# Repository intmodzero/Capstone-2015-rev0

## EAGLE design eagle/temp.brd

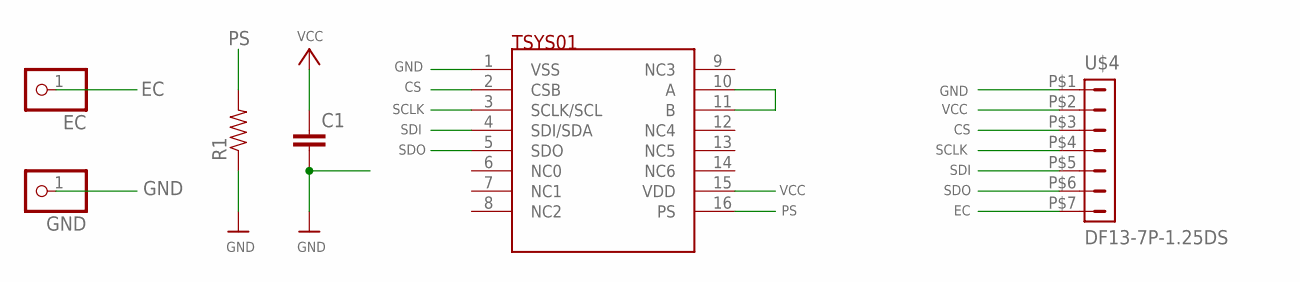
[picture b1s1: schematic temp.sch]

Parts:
C1: CAP0402-CAP; 0402-CAP
EC: PINHD-1X1; 1X01
GND: PINHD-1X1; 1X01
R1: RESISTOR0402-RES; 0402-RES
U$1: TSYS01; QFN16
U$4: DF13-7P-1.25DS

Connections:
CS: U$1.2 (CSB), U$4.P$3 (3)
EC: EC.1, U$4.P$7 (7)
GND: C1.2, GND.1, R1.1, U$1.1 (VSS), U$4.P$1 (1)
unnamed: U$1.10 (A), U$1.11 (B)
PS: R1.2, U$1.16 (PS)
SCLK: U$1.3 (SCLK/SCL), U$4.P$4 (4)
SDI: U$1.4 (SDI/SDA), U$4.P$5 (5)
SDO: U$1.5 (SDO), U$4.P$6 (6)
VCC: C1.1, U$1.15 (VDD), U$4.P$2 (2)

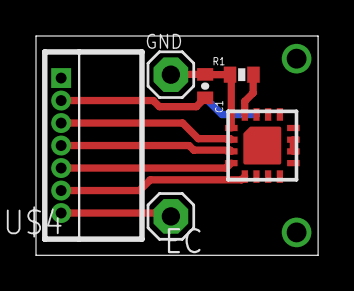
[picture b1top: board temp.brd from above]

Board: 2 copper layers, 15.7 x 12.2 mm, 6 parts (0 on the bottom side), 9 nets.

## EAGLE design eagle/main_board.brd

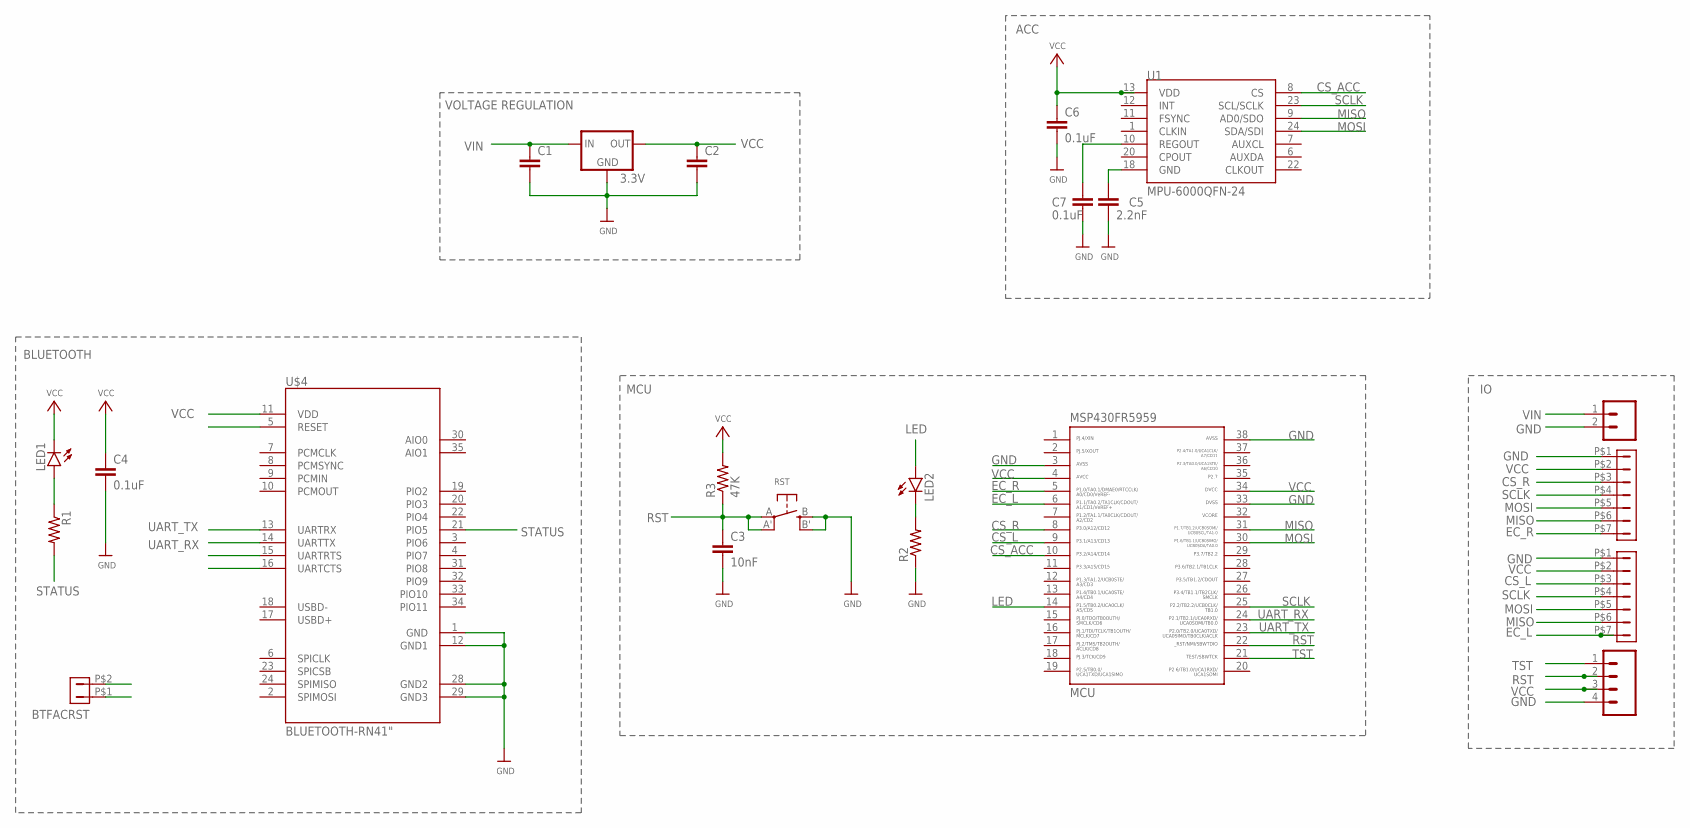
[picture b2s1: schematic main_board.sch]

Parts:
3.3V: V_REG_78XX; SOT223
5V: M02-JST-2-PTH-NO_SILK; JST-2-PTH-NS
BTFACRST: DF13-2P-1.25DSA
C1, C2: CAP0603-CAP; 0603-CAP
C3: 10nF; 0603-CAP
C4: 0.1uF; 0603-CAP
C5: 2.2nF; 0402-CAP
C6, C7: 0.1uF; 0402-CAP
LED1, LED2: LED0603; LED-0603
LEFT: DF13-7P-1.25DS
MCU: MSP430FR5959; TSSOP38_R-PDSO-G38-DA
PGM: M04JST; 1X04-1.5MM_JST
R1: RESISTOR0603-RES; 0603-RES
R2: RESISTOR0402-RES; 0402-RES
R3: 47K; 0402-RES
RIGHT: fname; DF13-7P-1.25DS
RST: SWITCH_TACT_SMT; EVQ-Q2
U1: MPU-6000QFN-24; QFN-24-TESTING
U$4: BLUETOOTH-RN41"; RN41

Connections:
BTRST: BTFACRST.P$2 (2), U$4.5 (RESET)
CS_ACC: MCU.10, U1.8 (CS)
CS_L: LEFT.P$3 (3), MCU.9
CS_R: MCU.8, RIGHT.P$3 (3)
EC_L: LEFT.P$7 (7), MCU.6
EC_R: MCU.5, RIGHT.P$7 (7)
GND: 3.3V.2 (GND), 3.3V.4 (GND), 5V.2, BTFACRST.P$1 (1), C1.2, C2.2, C3.2, C4.2, C5.2, C6.2, C7.2, LEFT.P$1 (1), MCU.3, MCU.33, MCU.38, PGM.4, R2.1, RIGHT.P$1 (1), RST.B (S), RST.B' (S1), U$4.1 (GND), U$4.12 (GND1), U$4.28 (GND2), U$4.29 (GND3)
LED: LED2.A, MCU.14
MISO: LEFT.P$6 (6), MCU.31, RIGHT.P$6 (6), U1.9 (AD0/SDO)
MOSI: LEFT.P$5 (5), MCU.30, RIGHT.P$5 (5), U1.24 (SDA/SDI)
unnamed: LED2.C, R2.2
unnamed: C7.1, U1.10 (REGOUT)
unnamed: C5.1, U1.18 (GND)
unnamed: LED1.A, R1.1
RST: C3.1, MCU.22, PGM.2, R3.1, RST.A, RST.A' (P1)
SCLK: LEFT.P$4 (4), MCU.25, RIGHT.P$4 (4), U1.23 (SCL/SCLK)
STATUS: R1.2, U$4.21 (PIO5)
TST: MCU.21, PGM.1
UART_RX: MCU.24, U$4.14 (UARTTX)
UART_TX: MCU.23, U$4.13 (UARTRX)
VCC: 3.3V.1 (OUT), C2.1, C4.1, C6.1, LED1.C, LEFT.P$2 (2), MCU.4, MCU.34, PGM.3, R3.2, RIGHT.P$2 (2), U1.13 (VDD), U$4.11 (VDD)
VIN: 3.3V.3 (IN), 5V.1, C1.1

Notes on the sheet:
MCU
BLUETOOTH
VOLTAGE REGULATION
ACC

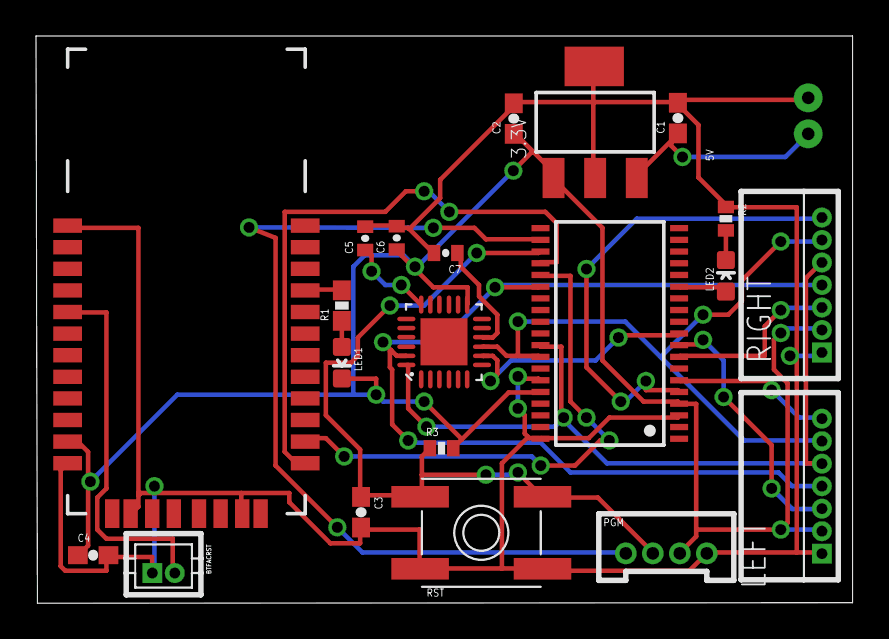
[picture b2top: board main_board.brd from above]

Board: 2 copper layers, 45.4 x 31.5 mm, 23 parts (0 on the bottom side), 22 nets.

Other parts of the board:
U$1: MMLOGO

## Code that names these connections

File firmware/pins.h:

#pragma once

#include "bitop.h"
#include "config.h"
#include "portmacros.h"

//UCA0
#define UART_PORT 2
#define UART_TX 0
#define UART_RX 1

#define UART_TS_PORT 4
#define UART_CTS 1
#define UART_RTS 2

#define LED_R_PORT 1
#define LED_R 5

#define SW_L_PORT 4
#define SW_L 5

#define SW_R_PORT 1
#define SW_R 1

// TSYS01 - Left and Right Fingers
#define TEMP_SPIIO_PORT 1
#define TEMP_MISO 7
#define TEMP_MOSI 6

#define TEMP_SCK_PORT 2
#define TEMP_SCK 2

#define TEMP_CS_PORT 3
#define TEMP_L_CS 1
#define TEMP_R_CS 0

#define ACC_SPIIO_PORT 1
#define ACC_MISO 7
#define ACC_MOSI 6

#define ACC_SCK_PORT 2
#define ACC_SCK 2

#define ACC_CS_PORT 3
#define ACC_CS 2

#define acc_spi_send_receive spi_UCB0_send_receive
#define acc_spi_init spi_UCB0_init

#define EC_PORT 1
#define EC_L 1
#define EC_R 0

void pins_init();

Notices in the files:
parts and their libraries:
SparkFun-Connectors: Licensing: Creative Commons ShareAlike 4.0 International - https://creativecommons.org/licenses/by-sa/4.0
